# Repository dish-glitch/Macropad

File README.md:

# Macropad

A custom 3-key macropad with an SSD1306 OLED display, built on a Seeed Studio XIAO RP2040. Designed from scratch in KiCad and Fusion 360 as a learning project for PCB design and CAD.
It took me about 3 hours to learn how to use 360 and try to see if the PCB would fit into my case. It took me about 1 hour trying to figure out how KICAD worked with the schematic and routing.
## Features
- 3x Cherry MX mechanical switches
- SSD1306 128x64 OLED display showing CPU/GPU temperatures
- Seeed Studio XIAO RP2040 microcontroller
- Custom 3D printed case with Hack Club logo
- USB-C connectivity
## Pictures

## Components
| Part | Cost |
|------|------|
| Seeed Studio XIAO RP2040 | ~$6 |
| Cherry MX Switches (x3) | ~$3 |
| SSD1306 OLED Display | ~$4 |
| PCB (JLCPCB, 5 pack) | ~$5 |
| 3D Printed Case | ~$3 |
| M3 Screws | ~$1 |
| **Total** | **~$22** |

## Tools Used
- KiCad 9.0 — Schematic and PCB layout
- Fusion 360 — Case design
- CircuitPython — Firmware (coming soon)

## Project Status
- [x] Schematic
- [x] PCB Layout
- [x] Case Design
- [ ] Firmware
- [ ] Assembly

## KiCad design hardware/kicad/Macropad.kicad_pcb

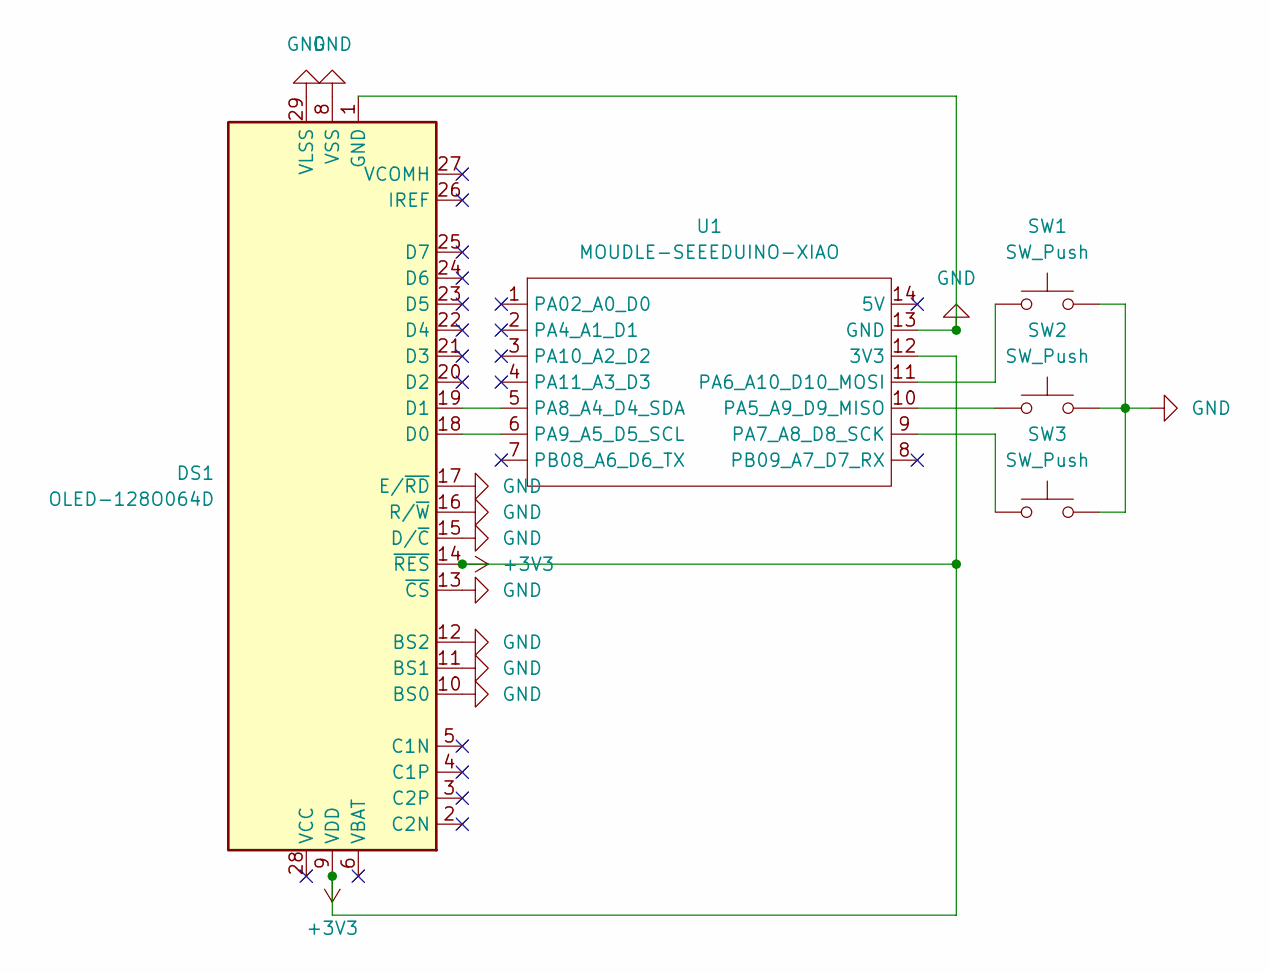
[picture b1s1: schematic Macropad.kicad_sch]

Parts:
DS1: OLED-128O064D
SW1, SW2, SW3: SW_Push; SW_Cherry_MX_1.00u_PCB
U1: MOUDLE-SEEEDUINO-XIAO; XIAO-Generic-Hybrid-14P-2.54-21X17.8MM

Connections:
+3V3: DS1.9 (VDD), DS1.14 (~RES), U1.12 (3V3)
GND: DS1.1 (GND), DS1.8 (VSS), DS1.10 (BS0), DS1.11 (BS1), DS1.12 (BS2), DS1.13 (~CS), DS1.15 (D/~C), DS1.16 (R/~W), DS1.17 (E/~RD), DS1.29 (VLSS), DS1.30 (GND), SW1.2, SW2.2, SW3.2, U1.13 (GND)
unnamed: DS1.18 (D0), U1.6 (PA9_A5_D5_SCL)
unnamed: DS1.19 (D1), U1.5 (PA8_A4_D4_SDA)
unnamed: SW2.1, U1.10 (PA5_A9_D9_MISO)
unnamed: SW1.1, U1.11 (PA6_A10_D10_MOSI)
unnamed: SW3.1, U1.9 (PA7_A8_D8_SCK)

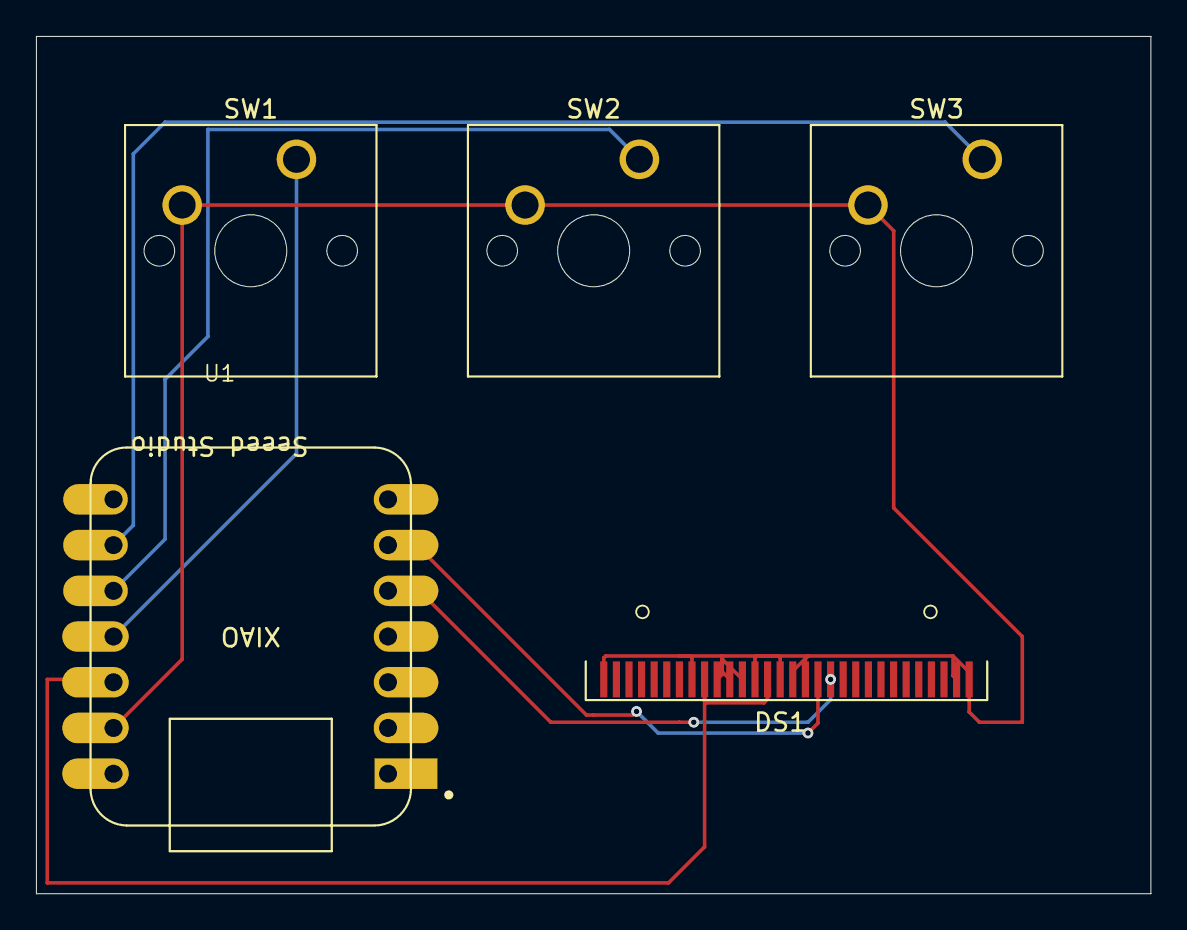
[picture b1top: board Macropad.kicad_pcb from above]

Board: 2 copper layers, 61.9 x 47.6 mm, 5 parts (0 on the bottom side), 7 nets.

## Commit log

2026-06-10 Create fusion360
